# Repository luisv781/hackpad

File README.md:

# luis's hackpad
This is a 4 key macropad with an OLED display and KMK firmware.

| Schematic | PCB | Case |
|-----------|-----|------|
||||

## Bill of Materials
- 1x Seeed XIAO RP2040
- 4x MX-Style switches
- 4x Blank DSA keycaps
- 1x 0.91" OLED display
- 2x SK6812 MINI-E LEDs
- 4x M3x5mx4mm heatset inserts
- 4x M3x16mm screws

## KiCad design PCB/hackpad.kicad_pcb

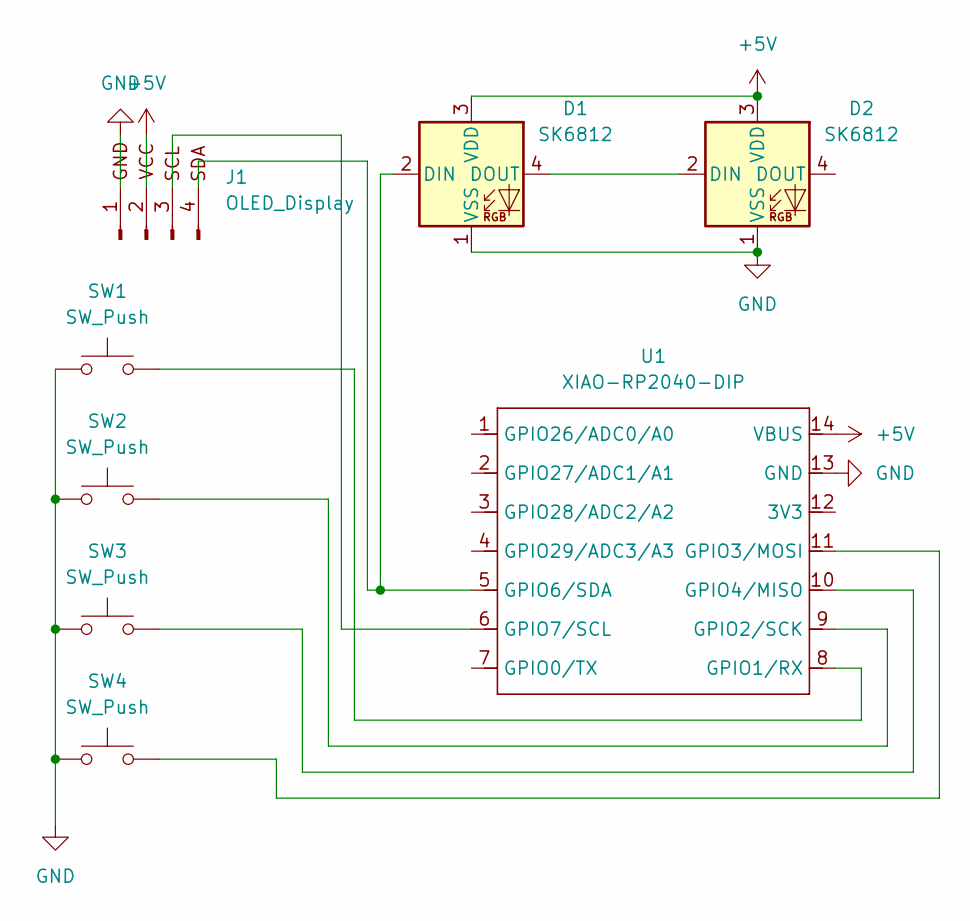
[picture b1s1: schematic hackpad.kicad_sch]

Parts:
D1, D2: SK6812; LED_SK6812MINI_PLCC4_3.5x3.5mm_P1.75mm
J1: OLED_Display; SSD1306-0.91-OLED-4pin-128x32
SW1, SW2, SW3, SW4: SW_Push; SW_Cherry_MX_1.00u_PCB
U1: XIAO-RP2040-DIP

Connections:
+5V: D1.3 (VDD), D2.3 (VDD), J1.2 (VCC), U1.14 (VBUS)
GND: D1.1 (VSS), D2.1 (VSS), J1.1 (GND), SW1.1, SW2.1, SW3.1, SW4.1, U1.13 (GND)
unnamed: D1.2 (DIN), J1.4 (SDA), U1.5 (GPIO6/SDA)
unnamed: D1.4 (DOUT), D2.2 (DIN)
unnamed: J1.3 (SCL), U1.6 (GPIO7/SCL)
unnamed: SW1.2, U1.8 (GPIO1/RX)
unnamed: SW2.2, U1.9 (GPIO2/SCK)
unnamed: SW4.2, U1.11 (GPIO3/MOSI)
unnamed: SW3.2, U1.10 (GPIO4/MISO)

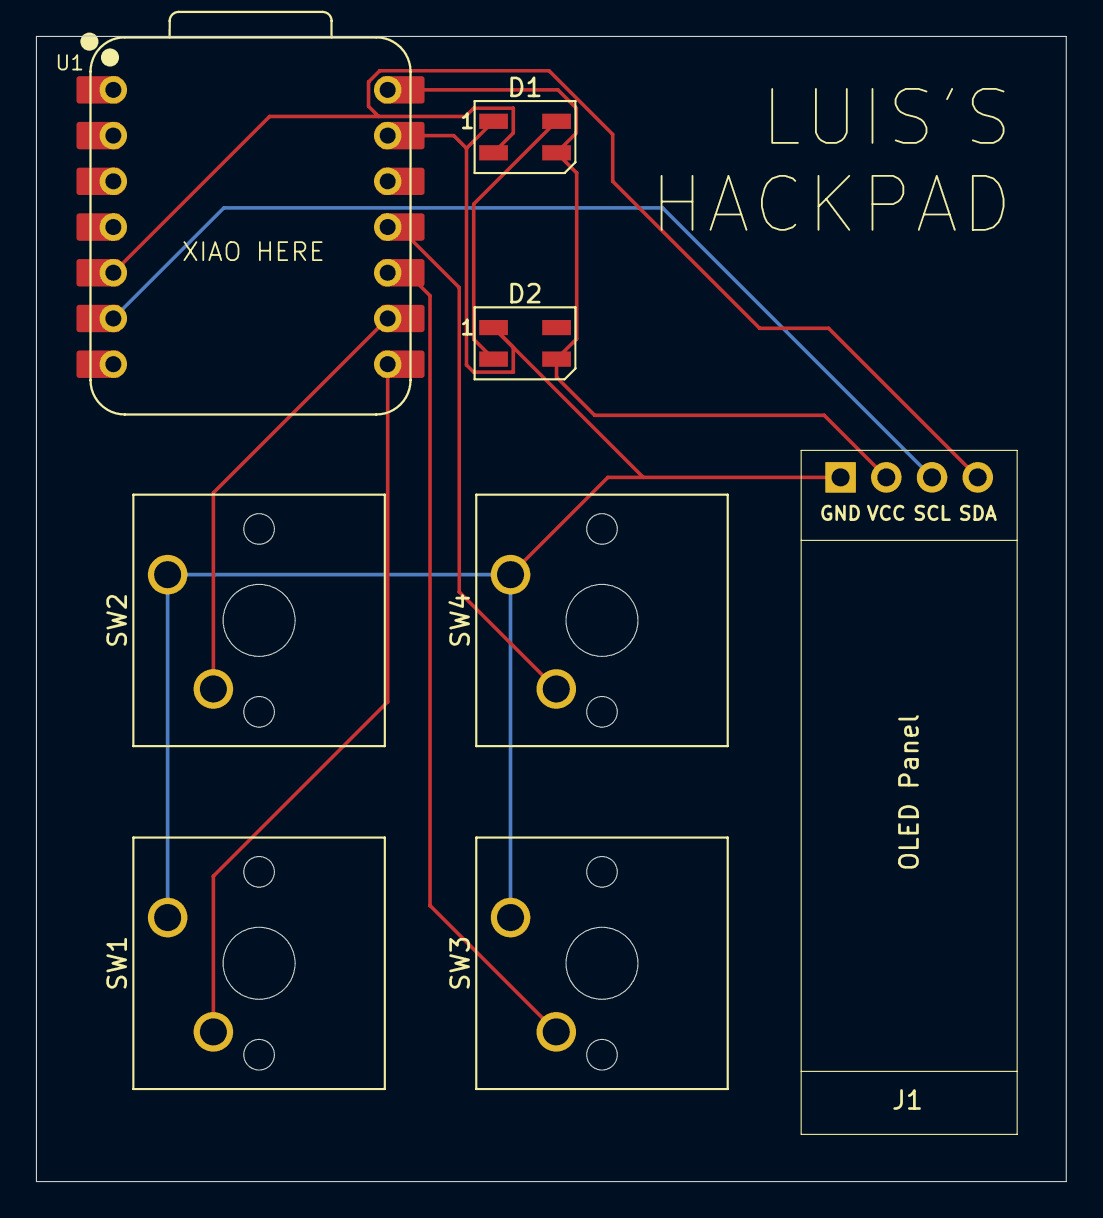
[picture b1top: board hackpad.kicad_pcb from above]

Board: 2 copper layers, 57.2 x 63.6 mm, 8 parts (0 on the bottom side), 9 nets.

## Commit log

2026-01-02 Uploaded Files
2026-01-03 Updated CAD
2026-01-03 Case with PCB
2026-01-03 Revise README for project name and details
2026-01-03 Add full render
2026-01-03 CAD Files
